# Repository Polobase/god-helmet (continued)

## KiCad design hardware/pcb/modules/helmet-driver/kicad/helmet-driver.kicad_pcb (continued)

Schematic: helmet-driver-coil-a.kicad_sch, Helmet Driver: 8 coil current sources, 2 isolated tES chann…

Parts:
C61, C64, C67, C70: 4.7n C0G; C_0603_1608Metric; MPN GRM1885C1H472JA01D; LCSC C85980
C62, C65, C68, C71: 2.2n C0G; C_0603_1608Metric; MPN 0603CG222J500NT; LCSC C2991172
C63, C66, C69, C72: 47n; C_0603_1608Metric; MPN CL10B473KB8NNNC; LCSC C1622
D8, D11, D14, D17: BAS40-04; SOT-23; MPN BAS40-04LT1G; LCSC C78265
D9, D10, D12, D13, D15, D16, D18, D19: SMF15CA; D_SOD-123F; MPN SMF15CA; LCSC C1851361
R43, R45, R48, R50, R53, R55, R58, R60: 10k; R_0603_1608Metric; MPN 0603WAF1002T5E; LCSC C25804
R44, R49, R54, R59: 47k; R_0603_1608Metric; MPN 0603WAF4702T5E; LCSC C25819
R46, R51, R56, R61: 10R; R_0603_1608Metric; MPN 0603WAF100JT5E; LCSC C22859
R47, R52, R57, R62: 124R; R_0603_1608Metric; MPN RN73H1JTTD1240B25; LCSC C346154
U1, U2: OPA2197; SOIC-8_3.9x4.9mm_P1.27mm; MPN OPA2197IDR; LCSC C139363
U7, U8: LM339B; SOIC-14_3.9x8.7mm_P1.27mm; MPN LM339BIDR; LCSC C22416291

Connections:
+15V: D8.2, D11.2, D14.2, D17.2; also elsewhere on the board
-15V: D8.1, D11.1, D14.1, D17.1; also elsewhere on the board
DAC1: R43.1; also elsewhere on the board
DAC2: R48.1; also elsewhere on the board
DAC3: R53.1; also elsewhere on the board
DAC4: R58.1; also elsewhere on the board
GND: C61.2, C63.2, C64.2, C66.2, C67.2, C69.2, C70.2, C72.2, D9.1 (A1), D10.1 (A1), D12.1 (A1), D13.1 (A1), D15.1 (A1), D16.1 (A1), D18.1 (A1), D19.1 (A1), R47.2, R52.2, R57.2, R62.2; also elsewhere on the board
unnamed: C62.1, R44.2
unnamed: C63.1, R46.2
unnamed: C65.1, R49.2
unnamed: C66.1, R51.2
unnamed: C68.1, R54.2
unnamed: C69.1, R56.2
unnamed: C71.1, R59.2
unnamed: C72.1, R61.2
unnamed: C61.1, R43.2, U1.3 (+)
unnamed: R44.1, R45.1, U1.2 (-)
unnamed: C64.1, R48.2, U1.5 (+)
unnamed: R49.1, R50.1, U1.6 (-)
unnamed: C67.1, R53.2, U2.3 (+)
unnamed: R54.1, R55.1, U2.2 (-)
unnamed: C70.1, R58.2, U2.5 (+)
unnamed: R59.1, R60.1, U2.6 (-)
OUT1: C62.2, D8.3, D9.2 (A2), R46.1, U1.1; also elsewhere on the board
OUT2: C65.2, D11.3, D12.2 (A2), R51.1, U1.7; also elsewhere on the board
OUT3: C68.2, D14.3, D15.2 (A2), R56.1, U2.1; also elsewhere on the board
OUT4: C71.2, D17.3, D18.2 (A2), R61.1, U2.7; also elsewhere on the board
TRIP_OC: U7.1, U7.2, U7.13, U7.14, U8.1, U8.2, U8.13, U8.14; also elsewhere on the board
VTH_N: U7.6 (-), U7.8 (-), U8.6 (-), U8.8 (-); also elsewhere on the board
VTH_P: U7.5 (+), U7.11 (+), U8.5 (+), U8.11 (+); also elsewhere on the board
X1: D10.2 (A2), R45.2, R47.1, U7.4 (-), U7.7 (+); also elsewhere on the board
X2: D13.2 (A2), R50.2, R52.1, U7.9 (+), U7.10 (-); also elsewhere on the board
X3: D16.2 (A2), R55.2, R57.1, U8.4 (-), U8.7 (+); also elsewhere on the board
X4: D19.2 (A2), R60.2, R62.1, U8.9 (+), U8.10 (-); also elsewhere on the board

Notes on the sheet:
Coil channel 4: 20.16 mA at full scale (2.5 V on 124 Ω)
Coil channel 2: 20.16 mA at full scale (2.5 V on 124 Ω)
Coil channel 1: 20.16 mA at full scale (2.5 V on 124 Ω)
Coil channel 3: 20.16 mA at full scale (2.5 V on 124 Ω)

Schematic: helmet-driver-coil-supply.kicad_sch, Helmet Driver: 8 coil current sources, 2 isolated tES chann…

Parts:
C85, C86, C87, C88, C89, C90, C91, C92, C93, C94, C95, C96, C97, C98, C99, C100: 100n; C_0603_1608Metric; MPN CC0603KRX7R9BB104; LCSC C14663
H1, H2, H3, H4: M3; MountingHole_3.2mm_M3; PartKey mounting-hole-m3
J4: 43045-1600; Molex_Micro-Fit_3.0_43045-1600_2x08_P3.00mm_Horizontal; MPN 430451600; LCSC C277731
U1, U2, U3, U4: OPA2197; SOIC-8_3.9x4.9mm_P1.27mm; MPN OPA2197IDR; LCSC C139363
U7, U8, U9, U10: LM339B; SOIC-14_3.9x8.7mm_P1.27mm; MPN LM339BIDR; LCSC C22416291

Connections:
+15V: C85.1, C87.1, C89.1, C91.1, C93.1, C95.1, C97.1, C99.1, U1.8 (V+), U2.8 (V+), U3.8 (V+), U4.8 (V+), U7.3 (V+), U8.3 (V+), U9.3 (V+), U10.3 (V+); also elsewhere on the board
-15V: C86.2, C88.2, C90.2, C92.2, C94.2, C96.2, C98.2, C100.2, U1.4 (V-), U2.4 (V-), U3.4 (V-), U4.4 (V-), U7.12 (V-), U8.12 (V-), U9.12 (V-), U10.12 (V-); also elsewhere on the board
GND: C85.2, C86.1, C87.2, C88.1, C89.2, C90.1, C91.2, C92.1, C93.2, C94.1, C95.2, C96.1, C97.2, C98.1, C99.2, C100.1; also elsewhere on the board
OUT1: J4.1; also elsewhere on the board
OUT2: J4.2; also elsewhere on the board
OUT3: J4.3; also elsewhere on the board
OUT4: J4.4; also elsewhere on the board
OUT5: J4.5; also elsewhere on the board
OUT6: J4.6; also elsewhere on the board
OUT7: J4.7; also elsewhere on the board
OUT8: J4.8; also elsewhere on the board
X1: J4.9; also elsewhere on the board
X2: J4.10; also elsewhere on the board
X3: J4.11; also elsewhere on the board
X4: J4.12; also elsewhere on the board
X5: J4.13; also elsewhere on the board
X6: J4.14; also elsewhere on the board
X7: J4.15; also elsewhere on the board
X8: J4.16; also elsewhere on the board

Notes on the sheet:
Coil connector: Molex Micro-Fit 3.0, 2 x 8, latching. Coil k: pin k = OUTk (signal), pin k + 8 = Xk (return), side by side
Supplies of the coil drivers (OPA2197) and the trip comparators (LM339B), 100 nF per rail and chip
Mounting holes (M3)

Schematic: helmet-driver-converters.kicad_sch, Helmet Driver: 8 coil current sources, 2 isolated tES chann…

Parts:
C39: 10u 50V; C_1206_3216Metric; MPN CL31A106KBHNNNE; LCSC C13585
C40: 220n; C_0603_1608Metric; MPN CL10B224KB8NNNC; LCSC C64705
C41: 330p C0G; C_0603_1608Metric; MPN 0603CG331J500NT; LCSC C190577
C42, C43, C44, C45, C46, C47, C48: 100n; C_0603_1608Metric; MPN CC0603KRX7R9BB104; LCSC C14663
C49, C53, C54, C55, C59, C60: 10u 25V; C_1210_3225Metric; MPN CL32B106KAJNNNE; LCSC C39232
C50, C52, C56, C58: 1u 25V; C_0603_1608Metric; MPN CL10B105KA8NNNC; LCSC C29936
C51, C57: 22u 25V; C_1210_3225Metric; MPN CL32B226KAJNNNE; LCSC C309062
FB3: 600R; L_0805_2012Metric; MPN GZ2012D601TF; LCSC C1017
R42: 33R; R_0603_1608Metric; MPN 0603WAF330JT5E; LCSC C23140
TP5: TP; TestPoint_2Pads_Pitch2.54mm_Drill0.8mm; PartKey testpoint-2pad
U23: DAC81408; Texas_RHA_VQFN-40-1EP_6x6mm_P0.5mm_EP4.6x4.6mm_ThermalVias; MPN DAC81408RHAR; LCSC C2680134
U24, U25: ADS8688; TSSOP-38_4.4x9.7mm_P0.5mm; MPN ADS8688IDBTR; LCSC C527390

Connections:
+3V3: C48.1, C54.1, C60.1, U23.9 (VIO), U23.20 (~CLR), U24.2 (~RST/PD), U24.34 (DVDD), U25.2 (~RST/PD), U25.34 (DVDD); also elsewhere on the board
+5V: FB3.1; also elsewhere on the board
+5VA: C39.1, C46.1, C47.1, C52.1, C53.1, C58.1, C59.1, FB3.2, U23.37 (VAA), U23.38 (VDD), U24.9 (AVDD), U24.30 (AVDD), U25.9 (AVDD), U25.30 (AVDD)
+15V: C42.1, C43.1, U23.31 (VCC), U23.40 (VCC); also elsewhere on the board
-15V: C44.2, C45.2, U23.32 (V-), U23.39 (V-); also elsewhere on the board
/DAC81408 and the monitor ADCs (ADS8688)/ADCO_REFCAP: C56.1, C57.1, U25.7 (REFCAP)
/DAC81408 and the monitor ADCs (ADS8688)/ADCO_REFIO: C55.1, U25.5 (REFIO)
/DAC81408 and the monitor ADCs (ADS8688)/ADCX_REFCAP: C50.1, C51.1, U24.7 (REFCAP)
/DAC81408 and the monitor ADCs (ADS8688)/ADCX_REFIO: C49.1, U24.5 (REFIO)
/DAC81408 and the monitor ADCs (ADS8688)/ADC_DAISY: U24.3 (DAISY), U25.36 (SDO)
/DAC81408 and the monitor ADCs (ADS8688)/VREF: C40.1, TP5.1, U23.33 (REF)
CS_ADC: U24.38 (~CS), U25.38 (~CS); also elsewhere on the board
CS_DAC: U23.14 (~CS); also elsewhere on the board
DAC1: U23.5 (OUT0); also elsewhere on the board
DAC2: U23.6 (OUT1); also elsewhere on the board
DAC3: U23.7 (OUT2); also elsewhere on the board
DAC4: U23.8 (OUT3); also elsewhere on the board
DAC5: U23.23 (OUT4); also elsewhere on the board
DAC6: U23.24 (OUT5); also elsewhere on the board
DAC7: U23.25 (OUT6); also elsewhere on the board
DAC8: U23.26 (OUT7); also elsewhere on the board
DAC_RST_N: U23.19 (~RESET); also elsewhere on the board
GND: C39.2, C40.2, C41.2, C42.2, C43.2, C44.1, C45.1, C46.2, C47.2, C48.2, C49.2, C50.2, C51.2, C52.2, C53.2, C54.2, C55.2, C56.2, C57.2, C58.2, C59.2, C60.2, TP5.2, U23.10 (GND), U23.15 (TOGGLE0), U23.16 (TOGGLE1), U23.17 (TOGGLE2), U23.35 (REFGND), U23.36 (GND), U23.41 (PAD), U24.4 (~REFSEL), U24.6 (REFGND), U24.8 (AGND), U24.10 (AUX_IN), U24.11 (AUX_GND), U24.13 (AIN_6GND), U24.15 (AIN_7GND), U24.17 (AIN_0GND), U24.19 (AIN_1GND), U24.20 (AIN_2GND), U24.22 (AIN_3GND), U24.24 (AIN_4GND), U24.26 (AIN_5GND), U24.28 (AGND), U24.29 (AGND), U24.31 (AGND), U24.32 (AGND), U24.33 (DGND), U25.3 (DAISY), U25.4 (~REFSEL), U25.6 (REFGND), U25.8 (AGND), U25.10 (AUX_IN), U25.11 (AUX_GND), U25.13 (AIN_6GND), U25.15 (AIN_7GND), U25.17 (AIN_0GND), U25.19 (AIN_1GND), U25.20 (AIN_2GND), U25.22 (AIN_3GND), U25.24 (AIN_4GND), U25.26 (AIN_5GND), U25.28 (AGND), U25.29 (AGND), U25.31 (AGND), U25.32 (AGND), U25.33 (DGND); also elsewhere on the board
LDAC: U23.18 (~LDAC); also elsewhere on the board
MISO: R42.1, U24.36 (SDO); also elsewhere on the board
MOSI: U23.13 (SDI), U24.1 (SDI), U25.1 (SDI); also elsewhere on the board
unnamed: C41.1, U23.34 (REFCMP)
unnamed: R42.2, U23.11 (SDO)
OUT1: U25.16 (AIN_0P); also elsewhere on the board
OUT2: U25.18 (AIN_1P); also elsewhere on the board
OUT3: U25.21 (AIN_2P); also elsewhere on the board
OUT4: U25.23 (AIN_3P); also elsewhere on the board
OUT5: U25.25 (AIN_4P); also elsewhere on the board
OUT6: U25.27 (AIN_5P); also elsewhere on the board
OUT7: U25.12 (AIN_6P); also elsewhere on the board
OUT8: U25.14 (AIN_7P); also elsewhere on the board
SCLK: U23.12 (SCLK), U24.37 (SCLK), U25.37 (SCLK); also elsewhere on the board
X1: U24.16 (AIN_0P); also elsewhere on the board
X2: U24.18 (AIN_1P); also elsewhere on the board
X3: U24.21 (AIN_2P); also elsewhere on the board
X4: U24.23 (AIN_3P); also elsewhere on the board
X5: U24.25 (AIN_4P); also elsewhere on the board
X6: U24.27 (AIN_5P); also elsewhere on the board
X7: U24.12 (AIN_6P); also elsewhere on the board
X8: U24.14 (AIN_7P); also elsewhere on the board

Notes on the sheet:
Both on ±10.24 V (shared SDI: the same settings for both); ±20 V protected inputs, 1 MΩ
Above 10.24 V it reads full scale: an output at the rail still shows
DAC81408: DAC1-DAC8 (OUT0-OUT7) on the ±2.5 V range, straight into each channel's setpoint filter
+5VA for the DAC and the ADCs (ferrite and 10 µF)
ADS8688 #2: the drive voltages OUT1-OUT8; its SDO runs into #1's DAISY input
RESET from DAC_RST_N: while not armed or before the rails are up, every output is tied to ground (0 mA)
ADS8688 #1 (first on MISO): the coil currents, X1-X8 (I = X / 124 Ω)

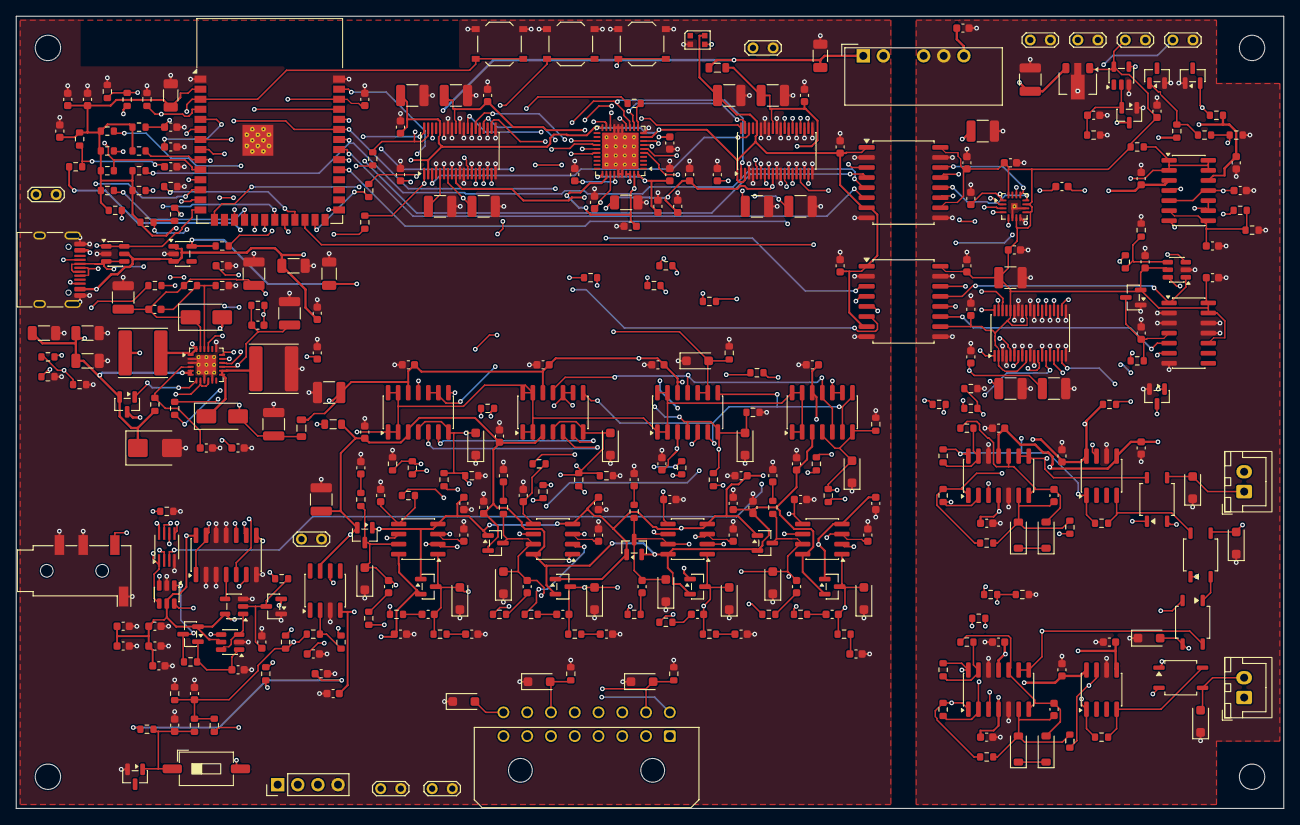
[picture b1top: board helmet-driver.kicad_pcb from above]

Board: 4 copper layers, 160.0 x 100.0 mm, 360 parts (0 on the bottom side), 198 nets.

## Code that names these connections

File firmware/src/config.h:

// Board wiring and fixed limits. One block per chip (docs/WIRING.md has the
// same tables); every block defines the same names, -1 = not present:
//   kSclk kMosi kSync kLdac  AD5328 module (kMiso only where an SD card shares the bus)
//   kArm                     PhotoMOS arming switch for the coil return
//   kStop                    external STOP button to GND
//   kBoot                    the board's BOOT button, a second STOP
//   kRgbLed / kStatusLed     status LED: addressable RGB, or a plain LED (high = on)
#pragma once
#include <cstdint>

#if defined(BOARD_HELMET_PCB)
// The helmet-driver board (hardware/pcb/modules/helmet-driver, rev B, untested): ESP32-S3-WROOM-1-N16R8, 8 current-
// source coil channels (DAC81408, +-20 mA, ceiling switch 5/20 mA, hardware trip latch), 2 isolated tES channels.
// Its GPIO table: hardware/pcb/modules/helmet-driver/spec.md. The esp32s3 map is kept where the two overlap.
namespace pins {
constexpr int kSclk = 12;   // -> SCLK of the DAC81408 and both ADS8688 (33 Ω)
constexpr int kMosi = 11;   // -> their SDI (33 Ω)
constexpr int kCsDac = 10;  // -> CS of the DAC81408 (10 kOhm pull-up)
constexpr int kCsAdc = 13;  // -> CS of both ADS8688 (daisy chain; 10 kOhm pull-up)
constexpr int kLdac = 9;    // -> LDAC of the DAC81408 (active low; 10 kOhm pull-up): loads all eight outputs
constexpr int kArm = 4;     // -> ARM (10 kOhm pull-down): enables the +-15 V rails with the latches clear
constexpr int kStop = 5;    // <- STOP button and jack (pull-up); the STOP latch is set in hardware as well
constexpr int kMiso = 3;     // <- the ADS8688 chain, and the DAC81408's readback (33 Ω). GPIO3 is a strapping pin
                             //    for the JTAG source only, ignored with the default eFuses (spec.md, GPIO table)
constexpr int kBoot = 0;
constexpr int kRgbLed = 48;  // WS2812B-2020
constexpr int kStatusLed = -1;
// Board only:
constexpr int kCeilAdc = 1;    // VTH_P through 10 kOhm: 0.684 V = 5 mA, 2.72 V = 20 mA
constexpr int kP15Adc = 2;     // +15 V / 11
constexpr int kN15Adc = 6;     // -15 V against 3.3 V (150k / 22k)
constexpr int kCc1Adc = 7, kCc2Adc = 8;  // USB-C CC voltages
constexpr int kTripQ = 14;     // <- TRIP latch Q (high = tripped)
constexpr int kStopQ = 15;     // <- STOP latch Q (high = STOP pressed)
constexpr int kClearN = 16;    // -> latch clear (low clears; a latch whose cause is still there stays set)
constexpr int kSda = 17, kScl = 18;  // the I2C header J3 only (a magnetometer); 4.7 kOhm pull-ups on the board
constexpr int kTesEn = 21;     // -> TES_EN (pull-down; gated with the STOP latch on the board)
constexpr int kTesSck = 38, kTesMosi = 39, kTesMiso = 40;  // island SPI through the ISO6741F
constexpr int kTesCsDac = 41, kTesCsAdc = 42;
constexpr int kTesFault = 44;  // <- island trip latch (high = tripped)
constexpr int kTesHeartbeat = 47;  // -> square wave, about 1 kHz, while tES runs
}  // namespace pins
#define BOARD_NAME "Helmet driver PCB"
#define HAS_PCB_DRIVER 1
#elif CONFIG_IDF_TARGET_ESP32S3
// ESP32-S3-DevKitC-1 (N8R8 / N16R8). Avoids strapping pins (0, 3, 45, 46),
// USB (19, 20), UART0 (43, 44) and the octal flash/PSRAM pins (26-37). FSPI default pins.
namespace pins {
constexpr int kSclk = 12;   // -> AD5328 module CLK
constexpr int kMosi = 11;   // -> DIN
constexpr int kSync = 10;   // -> SYNC (manual chip select, high between words)
constexpr int kLdac = 9;    // -> LDAC (pulse low: all 8 outputs update together)
constexpr int kArm = 4;     // -> PhotoMOS LED via 330 Ω, 10 kΩ pull-down: closes coil return
constexpr int kStop = 5;    // <- STOP button to GND (internal pull-up)
constexpr int kMiso = -1;   // not used
constexpr int kBoot = 0;
constexpr int kRgbLed = 48;  // DevKitC-1 v1.0 (v1.1 boards have it on 38)
constexpr int kStatusLed = -1;
}  // namespace pins
#define BOARD_NAME "ESP32-S3"
#elif CONFIG_IDF_TARGET_ESP32C3
// ESP32-C3-DevKitM-1, also the small "C3 Super Mini" boards (single core).
// Avoids strapping pins (2, 8, 9), USB (18, 19), UART0 (20, 21) and flash (12-17).
// FSPI default pins.
namespace pins {
constexpr int kSclk = 4;
constexpr int kMosi = 6;
constexpr int kSync = 7;
constexpr int kLdac = 5;
constexpr int kArm = 10;
constexpr int kStop = 3;
constexpr int kMiso = -1;
constexpr int kBoot = 9;
constexpr int kRgbLed = 8;   // DevKitM-1 RGB LED (a Super Mini's blue LED on 8 just flickers)
constexpr int kStatusLed = -1;
}  // namespace pins
#define BOARD_NAME "ESP32-C3"
#elif CONFIG_IDF_TARGET_ESP32C6
// ESP32-C6-DevKitC-1 (single core). Avoids strapping pins (4, 5, 8, 9, 15),
// USB (12, 13), UART0 (16, 17) and flash (24-30). FSPI default pins.
namespace pins {
constexpr int kSclk = 21;
constexpr int kMosi = 19;
constexpr int kSync = 18;
constexpr int kLdac = 20;
constexpr int kArm = 22;
constexpr int kStop = 23;
constexpr int kMiso = -1;
constexpr int kBoot = 9;
constexpr int kRgbLed = 8;
constexpr int kStatusLed = -1;
}  // namespace pins
#define BOARD_NAME "ESP32-C6"
#elif defined(BOARD_ESP32E_LCD28)
// "2.8inch ESP32-32E Display" (LCDwiki E32R28T / E32N28T, ESP32-D0WD, 4 MB),
// standalone: touchscreen UI, programs on the microSD card (docs/STANDALONE.md).
// The AD5328 sits on the 4-pin SPI peripheral header and shares the VSPI bus
// with the SD card. No arming switch (coil returns go to module GND) and no
// external STOP button: STOP is the on-screen button and the BOOT button.
namespace pins {
constexpr int kSclk = 18;   // SPI header SCK (shared with the SD card)
constexpr int kMosi = 23;   // SPI header MOSI (shared)
constexpr int kMiso = 19;   // SD card data out (the AD5328 never answers)
constexpr int kSync = 27;   // SPI header CS
constexpr int kLdac = -1;   // no free pin: module LDAC tied to 3.3 V, software single update
constexpr int kArm = -1;    // no arming switch
constexpr int kStop = 0;    // BOOT button (on-board 10 kΩ pull-up)
constexpr int kBoot = 0;    // the same button
constexpr int kRgbLed = -1, kStatusLed = -1;  // its own RGB LED: kLedR/G/B below
constexpr int kSdCs = 5;
// LCD on HSPI (ILI9341 or ST7789), touch XPT2046 read bit-banged on its own pins.
constexpr int kLcdSclk = 14, kLcdMosi = 13, kLcdMiso = 12, kLcdCs = 15, kLcdDc = 2;
constexpr int kBacklight = 21;   // high = on (PWM)
constexpr int kTouchSclk = 25, kTouchMosi = 32, kTouchMiso = 39, kTouchCs = 33, kTouchIrq = 36;
constexpr int kAudioEnable = 4;  // low = amplifier on: held high (silent)
constexpr int kAudioOut = 26;
constexpr int kLedR = 22, kLedG = 16, kLedB = 17;  // RGB LED, common anode: low = on
}  // namespace pins
#define HAS_SD_CARD 1
#define BOARD_NAME "ESP32-32E 2.8in display"
#else
// ESP32 DevKitC (WROOM-32), VSPI.
namespace pins {
constexpr int kSclk = 18;
constexpr int kMosi = 23;
constexpr int kSync = 5;
constexpr int kLdac = 17;
constexpr int kArm = 26;
constexpr int kStop = 27;
constexpr int kMiso = -1;   // not used
constexpr int kBoot = 0;
constexpr int kRgbLed = -1;
constexpr int kStatusLed = 2;  // the blue LED of most ESP32 DevKit boards
}  // namespace pins
#define BOARD_NAME "ESP32"
#endif

namespace limits {
constexpr uint32_t kTickUs = 500;          // sequencer period: 2 kHz
constexpr uint32_t kSpiHz = 20000000;      // AD5328 accepts up to 30 MHz, DAC81408 up to 50 MHz
constexpr float kMaxFieldUT = 10.0f;       // absolute ceiling accepted from the app (at 20 mm)
#ifdef HAS_PCB_DRIVER
constexpr float kMaxTestMA = 20.0f;        // DC test current limit; the board's ceiling switch limits it further
#else
constexpr float kMaxTestMA = 4.6f;         // DC test current limit (hardware cap is 4.54 mA)
#endif
constexpr uint32_t kMaxTestSeconds = 120;
constexpr uint32_t kMinIntervalS = 72u * 3600u;  // Shakti guidance: >= 72 h between sessions
}  // namespace limits

constexpr const char* kFirmwareVersion = "0.4.1";
constexpr int kProtocolVersion = 1;
